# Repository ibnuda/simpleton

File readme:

# Simpleton

3x5+3 board which uses weact's blackpill dev board (stm32f401ccu6).

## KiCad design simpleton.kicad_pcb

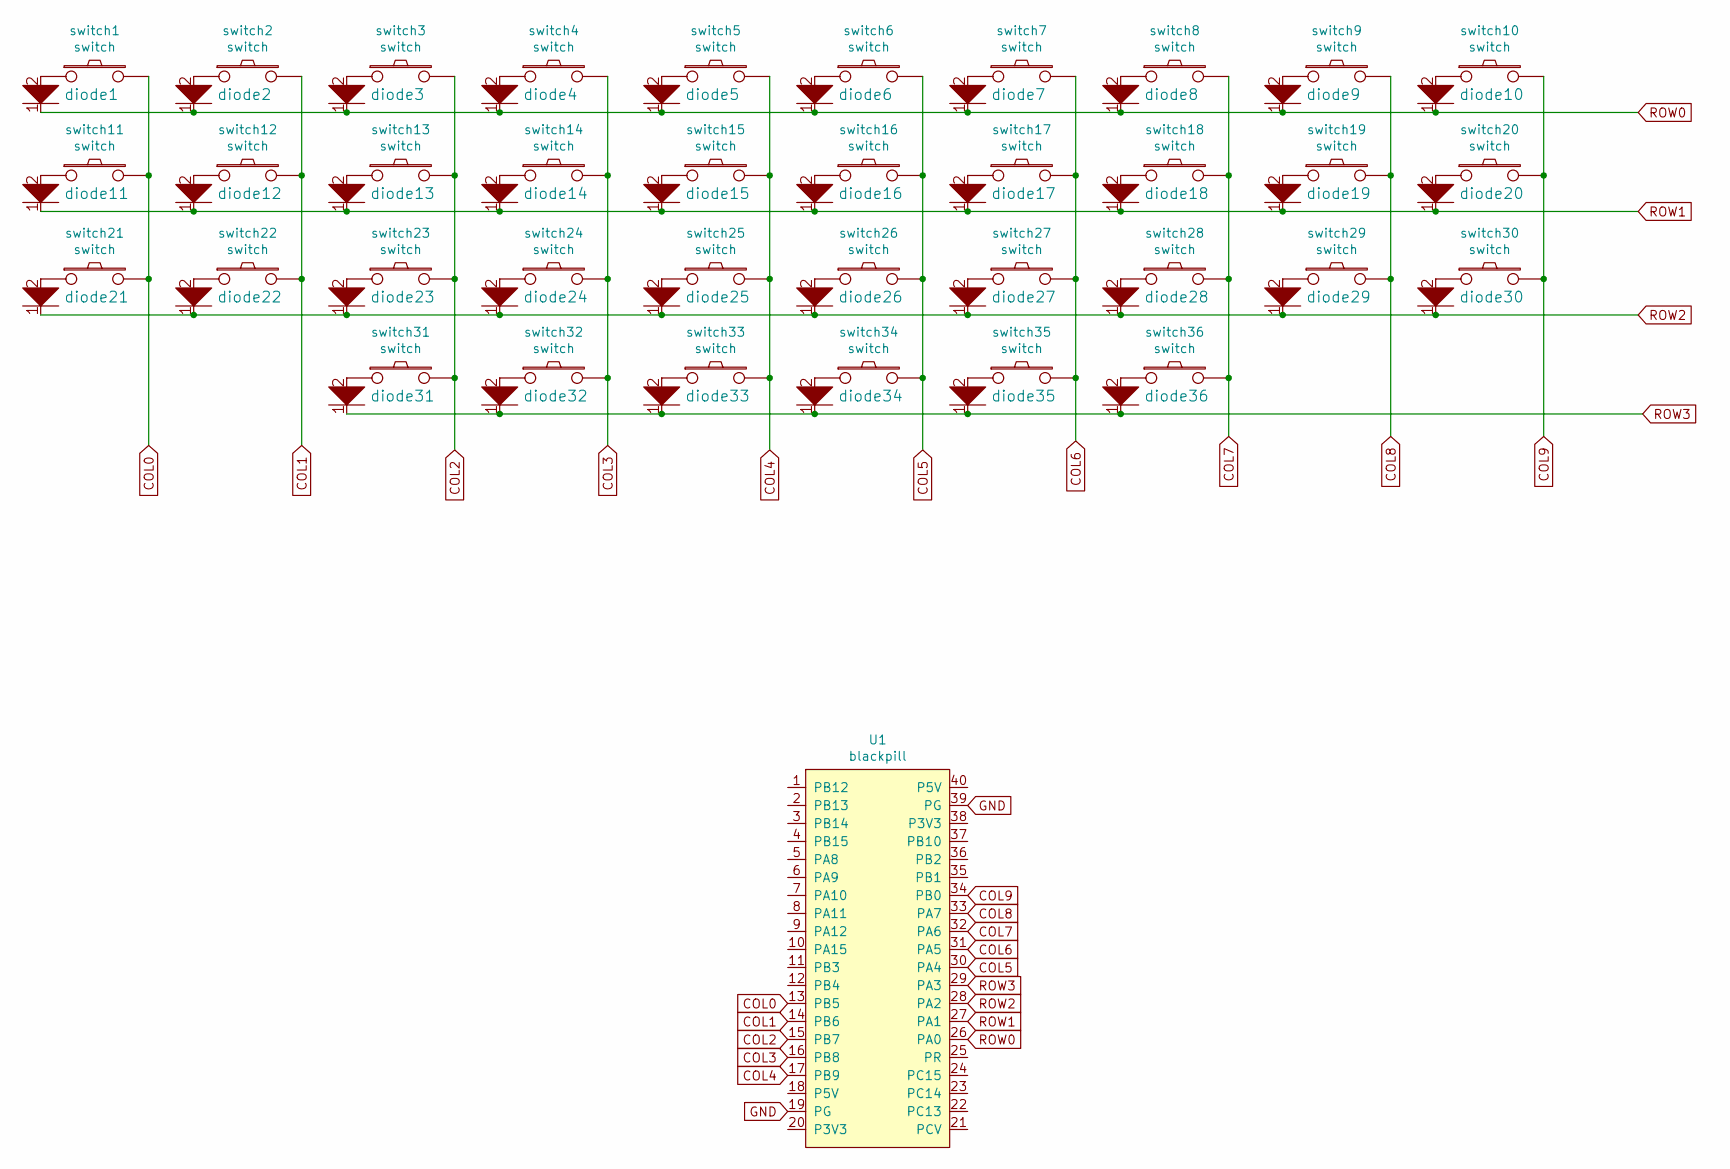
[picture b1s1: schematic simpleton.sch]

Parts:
U1: blackpill
diode1, diode2, diode3, diode4, diode5, diode6, diode7, diode8, diode9, diode10, diode11, diode12, diode13, diode14, diode15, diode16, diode17, diode18, diode19, diode20, diode21, diode22, diode23, diode24, diode25, diode26, diode27, diode28, diode29, diode30, diode31, diode32, diode33, diode34, diode35, diode36: diode
switch1, switch2, switch3, switch4, switch5, switch6, switch7, switch8, switch9, switch10, switch11, switch12, switch13, switch14, switch15, switch16, switch17, switch18, switch19, switch20, switch21, switch22, switch23, switch24, switch25, switch26, switch27, switch28, switch29, switch30, switch31, switch32, switch33, switch34, switch35, switch36: switch; 1u-minimal

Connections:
COL0: U1.13 (PB5), switch1.2, switch11.2, switch21.2
COL1: U1.14 (PB6), switch2.2, switch12.2, switch22.2
COL2: U1.15 (PB7), switch3.2, switch13.2, switch23.2, switch31.2
COL3: U1.16 (PB8), switch4.2, switch14.2, switch24.2, switch32.2
COL4: U1.17 (PB9), switch5.2, switch15.2, switch25.2, switch33.2
COL5: U1.30 (PA4), switch6.2, switch16.2, switch26.2, switch34.2
COL6: U1.31 (PA5), switch7.2, switch17.2, switch27.2, switch35.2
COL7: U1.32 (PA6), switch8.2, switch18.2, switch28.2, switch36.2
COL8: U1.33 (PA7), switch9.2, switch19.2, switch29.2
COL9: U1.34 (PB0), switch10.2, switch20.2, switch30.2
GND: U1.19 (PG), U1.39 (PG)
unnamed: diode1.2, switch1.1
unnamed: diode2.2, switch2.1
unnamed: diode3.2, switch3.1
unnamed: diode4.2, switch4.1
unnamed: diode5.2, switch5.1
unnamed: diode6.2, switch6.1
unnamed: diode7.2, switch7.1
unnamed: diode8.2, switch8.1
unnamed: diode9.2, switch9.1
unnamed: diode10.2, switch10.1
unnamed: diode11.2, switch11.1
unnamed: diode12.2, switch12.1
unnamed: diode13.2, switch13.1
unnamed: diode14.2, switch14.1
unnamed: diode15.2, switch15.1
unnamed: diode16.2, switch16.1
unnamed: diode17.2, switch17.1
unnamed: diode18.2, switch18.1
unnamed: diode19.2, switch19.1
unnamed: diode20.2, switch20.1
unnamed: diode21.2, switch21.1
unnamed: diode22.2, switch22.1
unnamed: diode23.2, switch23.1
unnamed: diode24.2, switch24.1
unnamed: diode25.2, switch25.1
unnamed: diode26.2, switch26.1
unnamed: diode27.2, switch27.1
unnamed: diode28.2, switch28.1
unnamed: diode29.2, switch29.1
unnamed: diode30.2, switch30.1
unnamed: diode31.2, switch31.1
unnamed: diode32.2, switch32.1
unnamed: diode33.2, switch33.1
unnamed: diode34.2, switch34.1
unnamed: diode35.2, switch35.1
unnamed: diode36.2, switch36.1
ROW0: U1.26 (PA0), diode1.1, diode2.1, diode3.1, diode4.1, diode5.1, diode6.1, diode7.1, diode8.1, diode9.1, diode10.1
ROW1: U1.27 (PA1), diode11.1, diode12.1, diode13.1, diode14.1, diode15.1, diode16.1, diode17.1, diode18.1, diode19.1, diode20.1
ROW2: U1.28 (PA2), diode21.1, diode22.1, diode23.1, diode24.1, diode25.1, diode26.1, diode27.1, diode28.1, diode29.1, diode30.1
ROW3: U1.29 (PA3), diode31.1, diode32.1, diode33.1, diode34.1, diode35.1, diode36.1

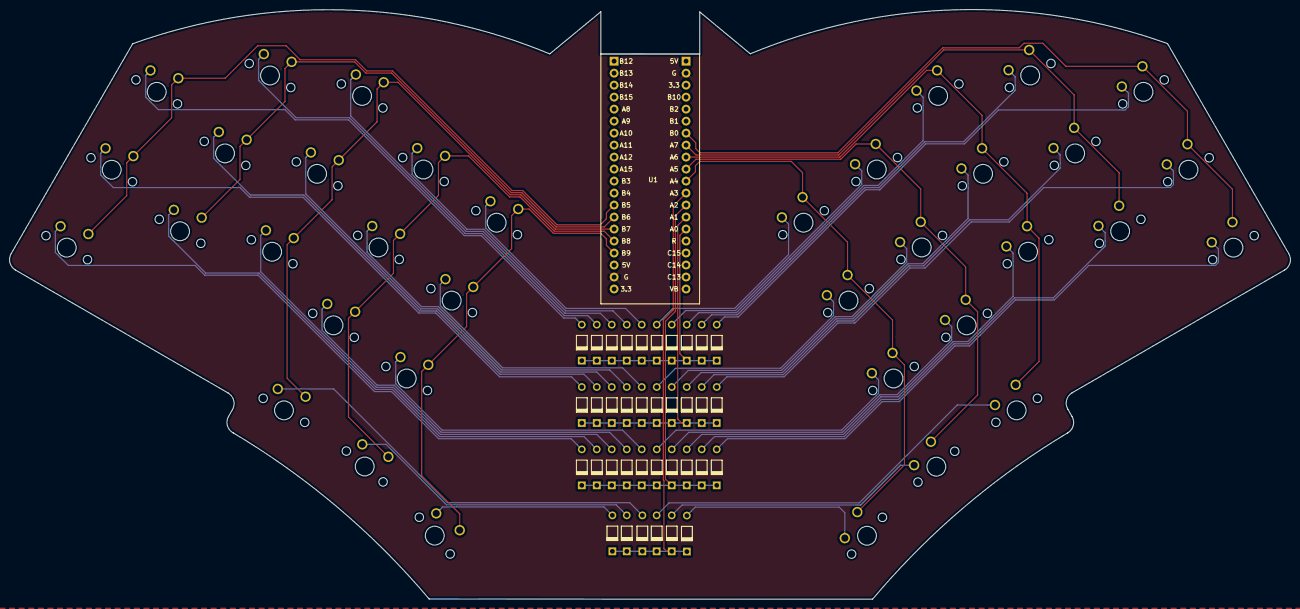
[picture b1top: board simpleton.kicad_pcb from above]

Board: 2 copper layers, 271.3 x 124.9 mm, 73 parts (0 on the bottom side), 51 nets.

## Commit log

2021-01-10 init commit.
2021-01-10 added readme.
2021-01-10 namtab.
2021-01-15 ground.
2021-01-16 refaktor skrip.
